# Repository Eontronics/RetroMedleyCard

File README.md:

# RetroMedleyCard
Repository containing the RetroMedleyCard hardware design files.

RetroMedleyCard is a buisiness card sized PCB created for the [Hackaday 2024 Business Card Contest](https://hackaday.io/contest/195949-2024-business-card-contest) that aims to run a range of emulators with support for USB controllers, and output to full sized monitors/TVs, while maintaining a thicnkess <=2.0mm.

The Hackaday.io project page for RetroMedleyCard may be found at https://hackaday.io/project/196328-retromedleycard, which includes images of the physical hardware and testing

# Limitations
The current (first) iteration of RetroMedleyCard is severely limited by the ~2MB of onboard RAM, and various other issues:
* It has been successfully tested running Gameboy emulation without audio output, however other emulators often cause the system to crash immediately.
* The connectors are all formed using specially shaped PCB structures in order to maintain a thin form-factor, however these often fail to make reliable contact for audio, USB-C and SD card connections.
* Display output is limited to ~52fps @320x240 in RGB565, due to difficulty moving pixel data from the RP2040 PIO into the frame-buffer while remaining syncronised with commands sent over the same interface

It is intended to run a modified version of [retro-go](https://github.com/ducalex/retro-go), however firmware is not yet provided as it is currently a mess of rushed tweaks in an attempt to get a functional device.

As a result of these limitations I do not see it being worthwhile to improve the firmware for this version of RetroMedleyCard, as future iterations should aim to adress the lack of available memory, for which a more complete firmware can be written.

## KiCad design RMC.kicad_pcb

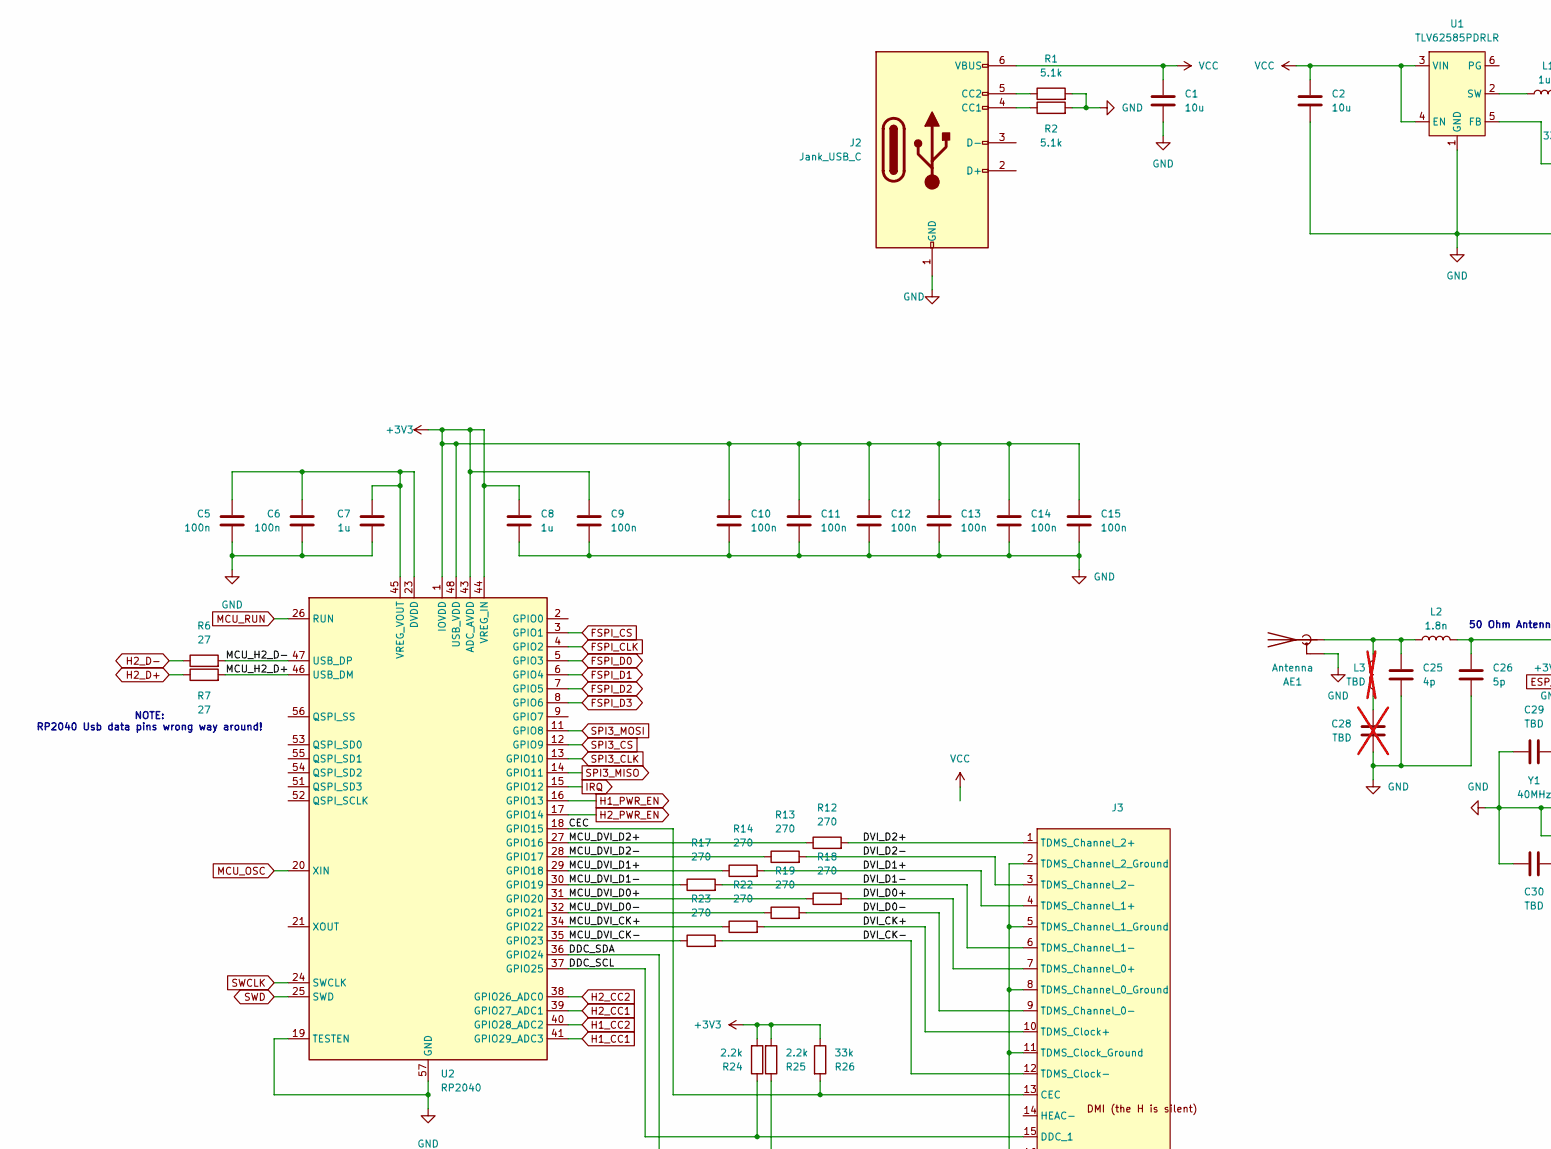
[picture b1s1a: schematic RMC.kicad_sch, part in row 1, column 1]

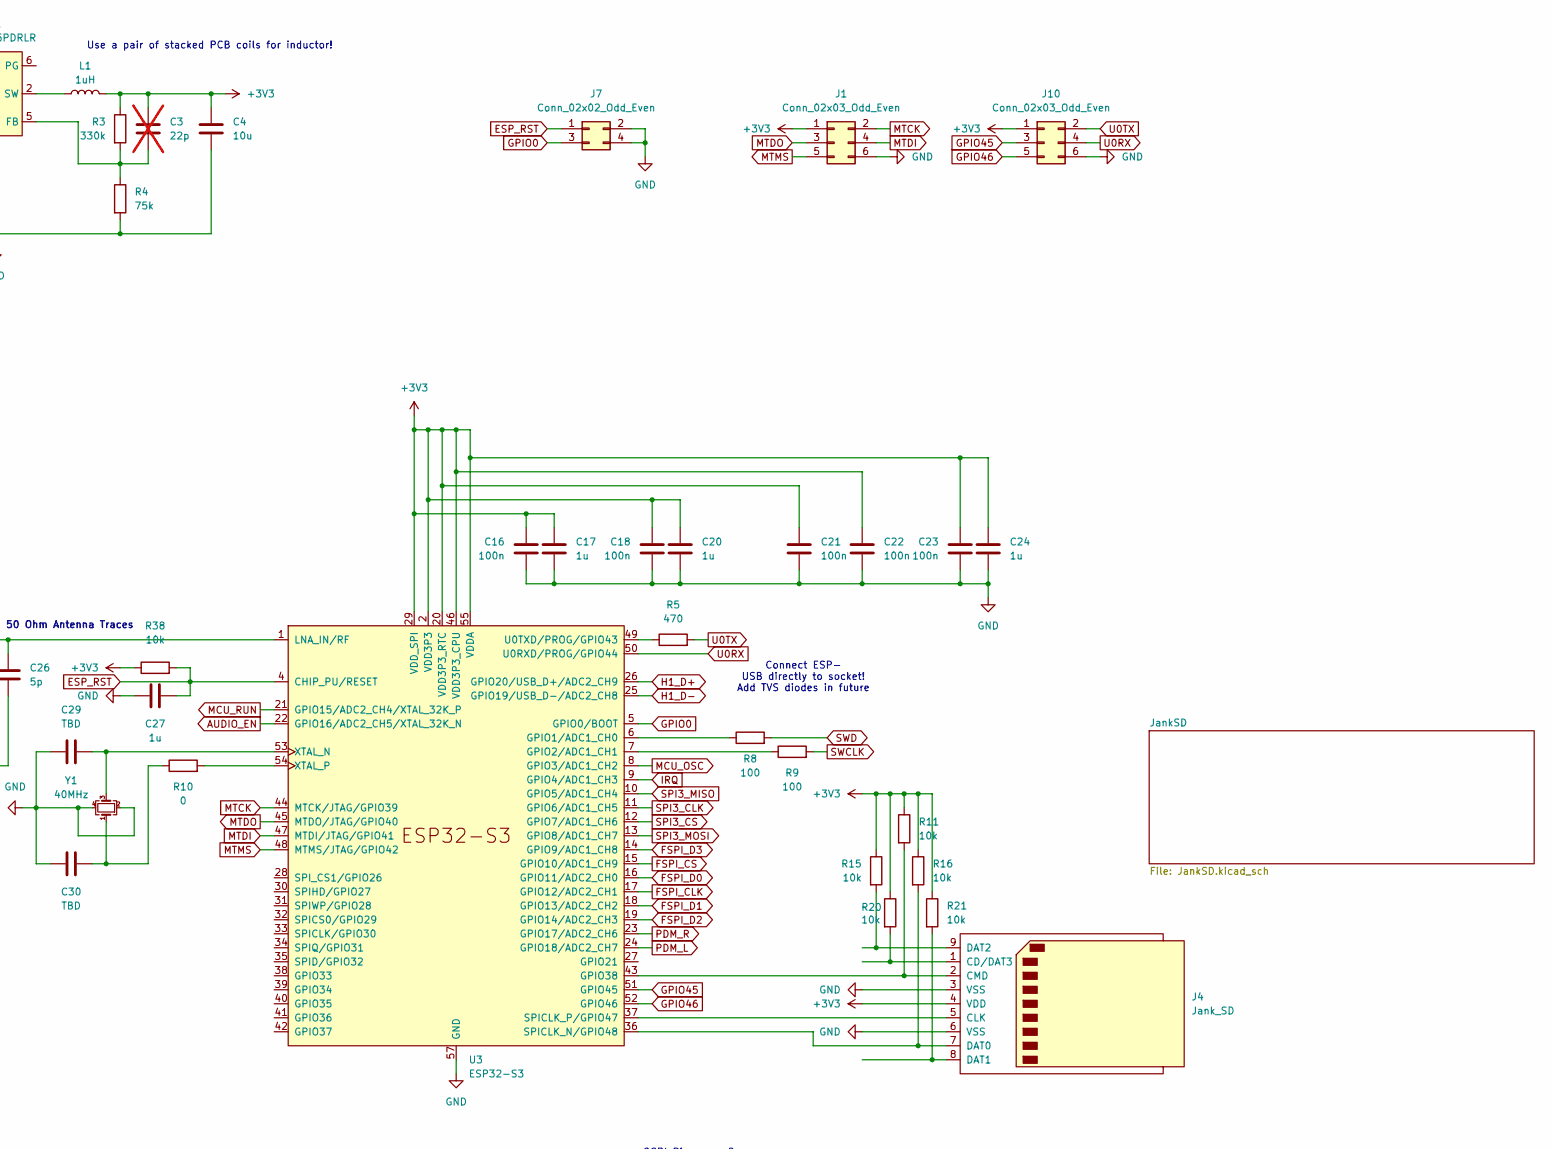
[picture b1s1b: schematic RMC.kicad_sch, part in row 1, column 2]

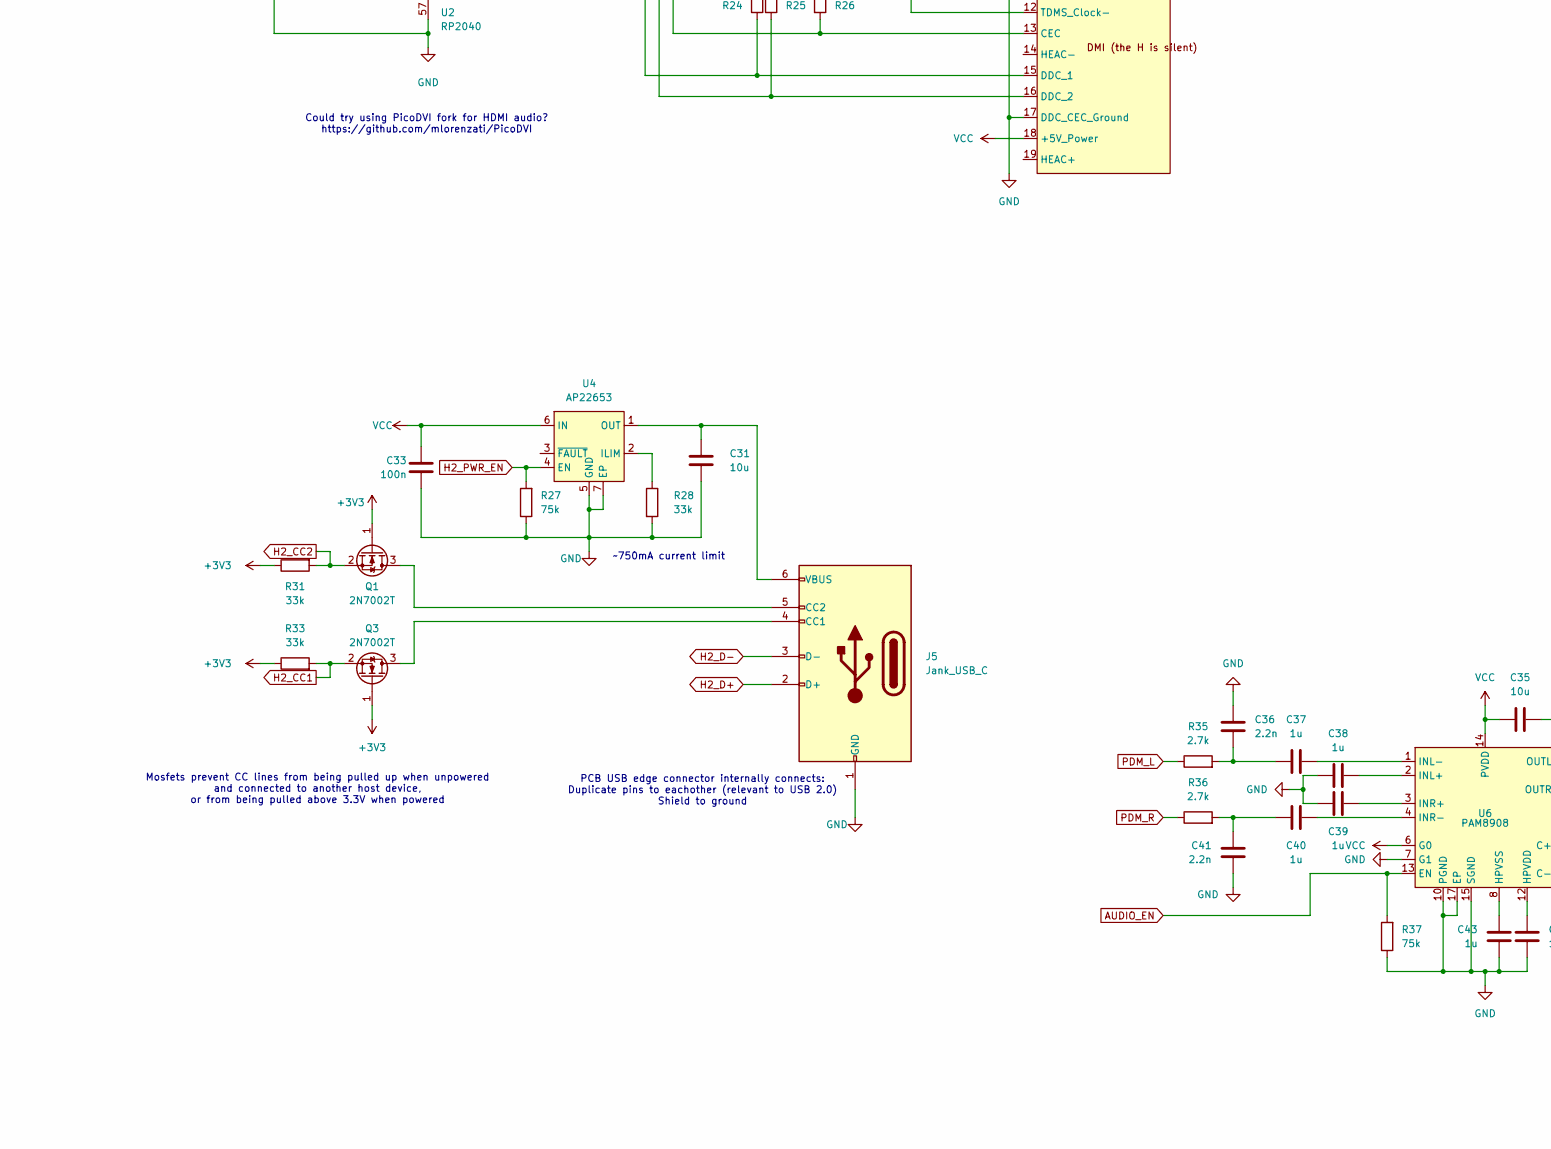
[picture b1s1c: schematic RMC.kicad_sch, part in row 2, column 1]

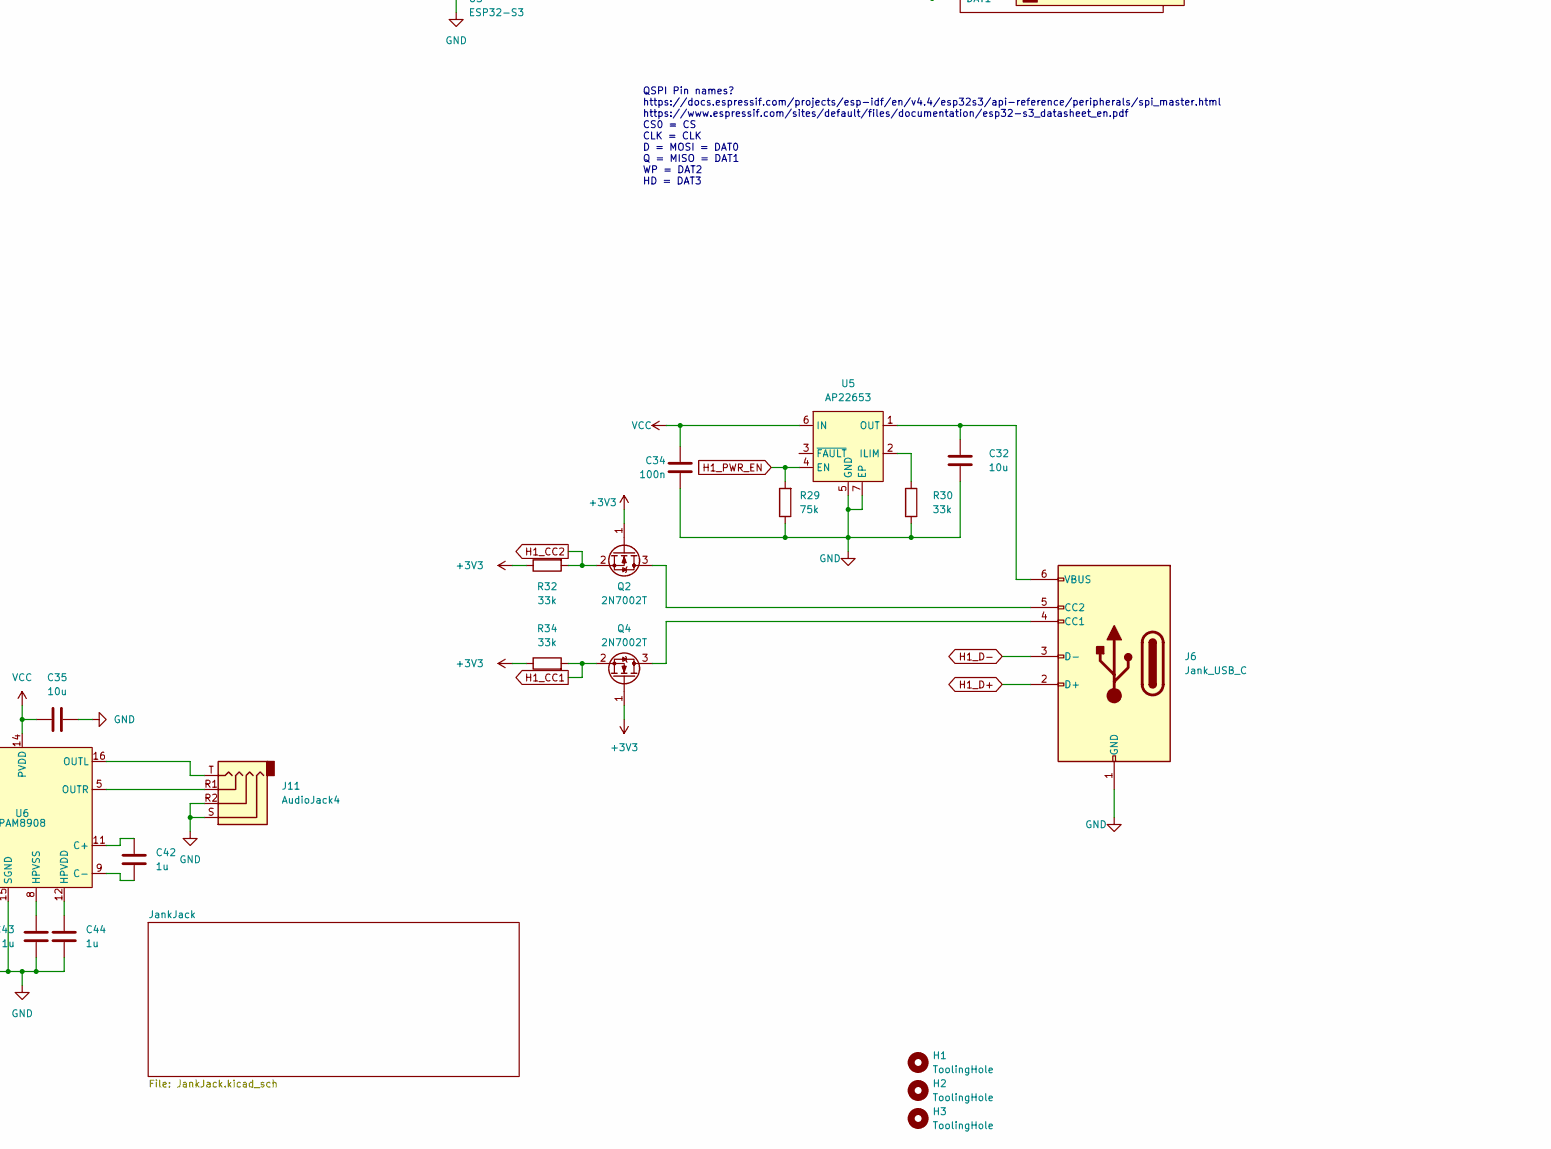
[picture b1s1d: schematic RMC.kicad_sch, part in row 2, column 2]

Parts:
AE1: Antenna; Texas_SWRA117D_2.4GHz_Right
C1, C2, C4, C31, C32, C35: 10u; C_0603_1608Metric
C3: 22p; C_0603_1608Metric; not fitted
C5, C6, C9, C10, C11, C12, C13, C14, C15, C16, C18, C21, C22, C23, C33, C34: 100n; C_0402_1005Metric
C7, C8, C17, C20, C24, C27, C37, C38, C39, C40, C42, C43, C44: 1u; C_0603_1608Metric
C25: 4p; C_0402_1005Metric
C26: 5p; C_0402_1005Metric
C28: TBD; C_0402_1005Metric; not fitted
C29, C30: TBD; C_0603_1608Metric
C36, C41: 2.2n; C_0603_1608Metric
H1, H2, H3: ToolingHole; JLC_Tooling_Hole
J1, J10: Conn_02x03_Odd_Even; PinHeader_2x03_P2.54mm_Vertical
J2, J5, J6: Jank_USB_C; JankUSBCB
J3: PBMI
J4: Jank_SD; JankSDB
J7: Conn_02x02_Odd_Even; PinHeader_2x02_P2.54mm_Vertical
J11: AudioJack4; JankJackB
L1: 1uH; 1uH_12.8mm_PCB_Coil
L2: 1.8n; L_0402_1005Metric
L3: TBD; L_0402_1005Metric; not fitted
Q1, Q2, Q3, Q4: 2N7002T; SOT-523
R1, R2: 5.1k; R_0603_1608Metric
R3: 330k; R_0603_1608Metric
R4, R27, R29, R37: 75k; R_0603_1608Metric
R5: 470; R_0603_1608Metric
R6, R7: 27; R_0603_1608Metric
R8, R9: 100; R_0603_1608Metric
R10: 0; R_0603_1608Metric
R11, R15, R16, R20, R21, R38: 10k; R_0603_1608Metric
R12, R13, R14, R17, R18, R19, R22, R23: 270; R_0603_1608Metric
R24, R25: 2.2k; R_0603_1608Metric
R26, R28, R30, R31, R32, R33, R34: 33k; R_0603_1608Metric
R35, R36: 2.7k; R_0603_1608Metric
U1: TLV62585PDRLR; SOT-563
U2: RP2040; QFN-56-1EP_7x7mm_P0.4mm_EP3.2x3.2mm
U3: ESP32-S3; QFN-56-1EP_7x7mm_P0.4mm_EP5.6x5.6mm
U4, U5: AP22653; DFN-6-1EP_2x2mm_P0.65mm_EP1x1.6mm
U6: PAM8908; QFN-16-1EP_3x3mm_P0.5mm_EP1.7x1.7mm
Y1: 40MHz; Crystal_SMD_3225-4Pin_3.2x2.5mm

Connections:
+3V3: C3.1, C4.1, C8.2, C9.1, C10.1, C11.1, C12.1, C13.1, C14.1, C15.1, C16.2, C17.2, C18.2, C20.2, C21.2, C22.2, C23.2, C24.2, J1.1, J4.4 (VDD), J10.1, L1.1, Q1.1 (G), Q2.1 (G), Q3.1 (G), Q4.1 (G), R3.1, R11.1, R15.1, R16.1, R20.1, R21.1, R24.2, R25.2, R26.1, R31.1, R32.1, R33.1, R34.1, R38.1, U2.1 (IOVDD), U2.10 (IOVDD), U2.22 (IOVDD), U2.33 (IOVDD), U2.42 (IOVDD), U2.43 (ADC_AVDD), U2.44 (VREG_IN), U2.48 (USB_VDD), U2.49 (IOVDD), U3.2 (VDD3P3), U3.3 (VDD3P3), U3.20 (VDD3P3_RTC), U3.29 (VDD_SPI), U3.46 (VDD3P3_CPU), U3.55 (VDDA), U3.56 (VDDA)
/CEC: J3.13 (CEC), R26.2, U2.18 (GPIO15)
/DDC_SCL: J3.15 (DDC_1), R24.1, U2.37 (GPIO25)
/DDC_SDA: J3.16 (DDC_2), R25.1, U2.36 (GPIO24)
/DVI_CK+: J3.10 (TDMS_Clock+), R22.2
/DVI_CK-: J3.12 (TDMS_Clock-), R23.2
/DVI_D0+: J3.7 (TDMS_Channel_0+), R18.2
/DVI_D0-: J3.9 (TDMS_Channel_0-), R19.2
/DVI_D1+: J3.4 (TDMS_Channel_1+), R14.2
/DVI_D1-: J3.6 (TDMS_Channel_1-), R17.2
/DVI_D2+: J3.1 (TDMS_Channel_2+), R12.2
/DVI_D2-: J3.3 (TDMS_Channel_2-), R13.2
/MCU_DVI_CK+: R22.1, U2.34 (GPIO22)
/MCU_DVI_CK-: R23.1, U2.35 (GPIO23)
/MCU_DVI_D0+: R18.1, U2.31 (GPIO20)
/MCU_DVI_D0-: R19.1, U2.32 (GPIO21)
/MCU_DVI_D1+: R14.1, U2.29 (GPIO18)
/MCU_DVI_D1-: R17.1, U2.30 (GPIO19)
/MCU_DVI_D2+: R12.1, U2.27 (GPIO16)
/MCU_DVI_D2-: R13.1, U2.28 (GPIO17)
/MCU_H2_D+: R7.2, U2.46 (USB_DM)
/MCU_H2_D-: R6.2, U2.47 (USB_DP)
AUDIO_EN: R37.2, U3.22 (GPIO16/ADC2_CH5/XTAL_32K_N), U6.13 (EN)
ESP_RST: C27.1, J7.1, R38.2, U3.4 (CHIP_PU/RESET)
FSPI_CLK: U2.4 (GPIO2), U3.17 (GPIO12/ADC2_CH1)
FSPI_CS: U2.3 (GPIO1), U3.15 (GPIO10/ADC1_CH9)
FSPI_D0: U2.5 (GPIO3), U3.16 (GPIO11/ADC2_CH0)
FSPI_D1: U2.6 (GPIO4), U3.18 (GPIO13/ADC2_CH2)
FSPI_D2: U2.7 (GPIO5), U3.19 (GPIO14/ADC2_CH3)
FSPI_D3: U2.8 (GPIO6), U3.14 (GPIO9/ADC1_CH8)
GND: AE1.2 (Shield), C1.1, C2.2, C4.2, C5.2, C6.2, C7.2, C8.1, C9.2, C10.2, C11.2, C12.2, C13.2, C14.2, C15.2, C16.1, C17.1, C18.1, C20.1, C21.1, C22.1, C23.1, C24.1, C25.2, C26.2, C27.2, C28.2, C29.1, C30.1, C31.2, C32.2, C33.2, C34.2, C35.1, C36.1, C38.1, C39.1, C41.2, C43.1, C44.1, J1.6, J2.1 (GND), J3.2 (TDMS_Channel_2_Ground), J3.5 (TDMS_Channel_1_Ground), J3.8 (TDMS_Channel_0_Ground), J3.11 (TDMS_Clock_Ground), J3.17 (DDC_CEC_Ground), J4.3 (VSS), J4.6 (VSS), J5.1 (GND), J6.1 (GND), J7.2, J7.4, J10.6, J11.R2, J11.S, R1.2, R2.2, R4.2, R27.1, R28.2, R29.1, R30.2, R37.1, U1.1 (GND), U2.19 (TESTEN), U2.57 (GND), U3.57 (GND), U4.5 (GND), U4.7 (EP), U5.5 (GND), U5.7 (EP), U6.7 (G1), U6.10 (PGND), U6.15 (SGND), U6.17 (EP), Y1.2, Y1.4
GPIO0: J7.3, U3.5 (GPIO0/BOOT)
GPIO45: J10.3, U3.51 (GPIO45)
GPIO46: J10.5, U3.52 (GPIO46)
H1_CC1: Q4.2 (S), R34.2, U2.41 (GPIO29_ADC3)
H1_CC2: Q2.2 (S), R32.2, U2.40 (GPIO28_ADC2)
H1_D+: J6.2 (D+), U3.26 (GPIO20/USB_D+/ADC2_CH9)
H1_D-: J6.3 (D-), U3.25 (GPIO19/USB_D-/ADC2_CH8)
H1_PWR_EN: R29.2, U2.16 (GPIO13), U5.4 (EN)
H2_CC1: Q3.2 (S), R33.2, U2.39 (GPIO27_ADC1)
H2_CC2: Q1.2 (S), R31.2, U2.38 (GPIO26_ADC0)
H2_D+: J5.2 (D+), R7.1
H2_D-: J5.3 (D-), R6.1
H2_PWR_EN: R27.2, U2.17 (GPIO14), U4.4 (EN)
IRQ: U2.15 (GPIO12), U3.9 (GPIO4/ADC1_CH3)
MCU_OSC: U2.20 (XIN), U3.8 (GPIO3/ADC1_CH2)
MCU_RUN: U2.26 (RUN), U3.21 (GPIO15/ADC2_CH4/XTAL_32K_P)
MTCK: J1.2, U3.44 (MTCK/JTAG/GPIO39)
MTDI: J1.4, U3.47 (MTDI/JTAG/GPIO41)
MTDO: J1.3, U3.45 (MTDO/JTAG/GPIO40)
MTMS: J1.5, U3.48 (MTMS/JTAG/GPIO42)
unnamed: AE1.1 (A), C25.1, L2.1, L3.2
unnamed: C28.1, L3.1
unnamed: C30.2, R10.1, Y1.1
unnamed: C36.2, C37.1, R35.2
unnamed: C40.1, C41.1, R36.2
unnamed: J2.4 (CC1), R2.1
unnamed: J2.5 (CC2), R1.1
unnamed: J4.1 (CD/DAT3), R20.2
unnamed: J4.5 (CLK), U3.37 (SPICLK_P/GPIO47)
unnamed: J4.2 (CMD), R11.2, U3.43 (GPIO38)
unnamed: J4.7 (DAT0), R16.2, U3.36 (SPICLK_N/GPIO48)
unnamed: J4.8 (DAT1), R21.2
unnamed: J4.9 (DAT2), R15.2
unnamed: J5.4 (CC1), Q3.3 (D)
unnamed: J5.5 (CC2), Q1.3 (D)
unnamed: C31.1, J5.6 (VBUS), U4.1 (OUT)
unnamed: J6.4 (CC1), Q4.3 (D)
unnamed: J6.5 (CC2), Q2.3 (D)
unnamed: C32.1, J6.6 (VBUS), U5.1 (OUT)
unnamed: C3.2, R3.2, R4.1, U1.5 (FB)
unnamed: L1.2, U1.2 (SW)
unnamed: C5.1, C6.1, C7.1, U2.23 (DVDD), U2.45 (VREG_VOUT), U2.50 (DVDD)
unnamed: R8.1, U3.6 (GPIO1/ADC1_CH0)
unnamed: R9.1, U3.7 (GPIO2/ADC1_CH1)
unnamed: C26.1, L2.2, U3.1 (LNA_IN/RF)
unnamed: R5.1, U3.49 (U0TXD/PROG/GPIO43)
unnamed: C29.2, U3.53 (XTAL_N), Y1.3
unnamed: R10.2, U3.54 (XTAL_P)
unnamed: R28.1, U4.2 (ILIM)
unnamed: R30.1, U5.2 (ILIM)
unnamed: C42.2, U6.11 (C+)
unnamed: C42.1, U6.9 (C-)
unnamed: C44.2, U6.12 (HPVDD)
unnamed: C43.2, U6.8 (HPVSS)
unnamed: C38.2, U6.2 (INL+)
unnamed: C37.2, U6.1 (INL-)
unnamed: C39.2, U6.3 (INR+)
unnamed: C40.2, U6.4 (INR-)
unnamed: J11.T, U6.16 (OUTL)
unnamed: J11.R1, U6.5 (OUTR)
PDM_L: R35.1, U3.24 (GPIO18/ADC2_CH7)
PDM_R: R36.1, U3.23 (GPIO17/ADC2_CH6)
SPI3_CLK: U2.13 (GPIO10), U3.11 (GPIO6/ADC1_CH5)
SPI3_CS: U2.12 (GPIO9), U3.12 (GPIO7/ADC1_CH6)
SPI3_MISO: U2.14 (GPIO11), U3.10 (GPIO5/ADC1_CH4)
SPI3_MOSI: U2.11 (GPIO8), U3.13 (GPIO8/ADC1_CH7)
SWCLK: R9.2, U2.24 (SWCLK)
SWD: R8.2, U2.25 (SWD)
U0RX: J10.4, U3.50 (U0RXD/PROG/GPIO44)
U0TX: J10.2, R5.2
VCC: C1.2, C2.1, C33.1, C34.1, C35.2, J2.6 (VBUS), J3.18 (+5V_Power), U1.3 (VIN), U1.4 (EN), U4.6 (IN), U5.6 (IN), U6.6 (G0), U6.14 (PVDD)

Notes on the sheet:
QSPI Pin names? https://docs.espressif.com/projects/esp-idf/en/v4.4/esp32s3/api-reference/peripherals/spi_master.html https://www.espressif.com/sites/default/files/documentation/esp32-s3_datasheet_en.pdf CS0 = CS CLK = CLK D = MOSI = DAT0 Q = MISO = DAT1 WP = DAT2 HD = DAT3
Use a pair of stacked PCB coils for inductor!
~750mA current limit
Connect ESP- USB directly to socket! Add TVS diodes in future
Could try using PicoDVI fork for HDMI audio? https://github.com/mlorenzati/PicoDVI
50 Ohm Antenna Traces
Mosfets prevent CC lines from being pulled up when unpowered and connected to another host device, or from being pulled above 3.3V when powered
NOTE: RP2040 Usb data pins wrong way around!
PCB USB edge connector internally connects: Duplicate pins to eachother (relevant to USB 2.0) Shield to ground

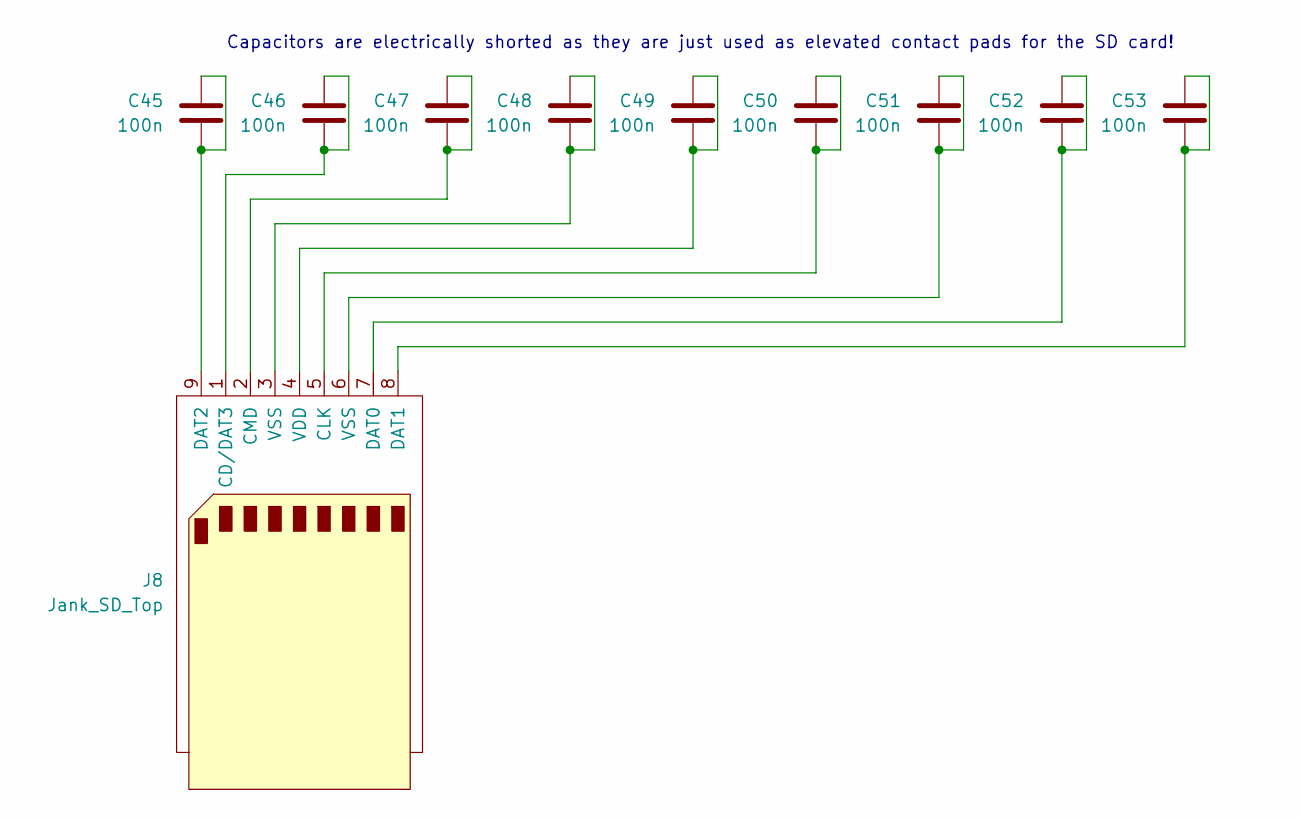
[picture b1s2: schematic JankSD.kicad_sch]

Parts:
C45, C46, C47, C48, C49, C50, C51, C52, C53: 100n; C_0603_1608Metric
J8: Jank_SD_Top; JankSDT

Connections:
unnamed: C48.1, C48.2, J8.3 (VSS)
unnamed: C51.1, C51.2, J8.6 (VSS)
unnamed: C46.1, C46.2, J8.1 (CD/DAT3)
unnamed: C50.1, C50.2, J8.5 (CLK)
unnamed: C47.1, C47.2, J8.2 (CMD)
unnamed: C52.1, C52.2, J8.7 (DAT0)
unnamed: C53.1, C53.2, J8.8 (DAT1)
unnamed: C45.1, C45.2, J8.9 (DAT2)
unnamed: C49.1, C49.2, J8.4 (VDD)

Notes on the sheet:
Capacitors are electrically shorted as they are just used as elevated contact pads for the SD card!

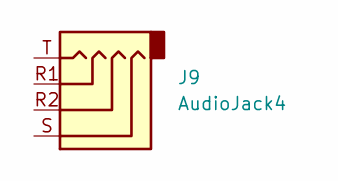
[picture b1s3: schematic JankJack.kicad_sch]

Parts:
J9: AudioJack4; JankJackT

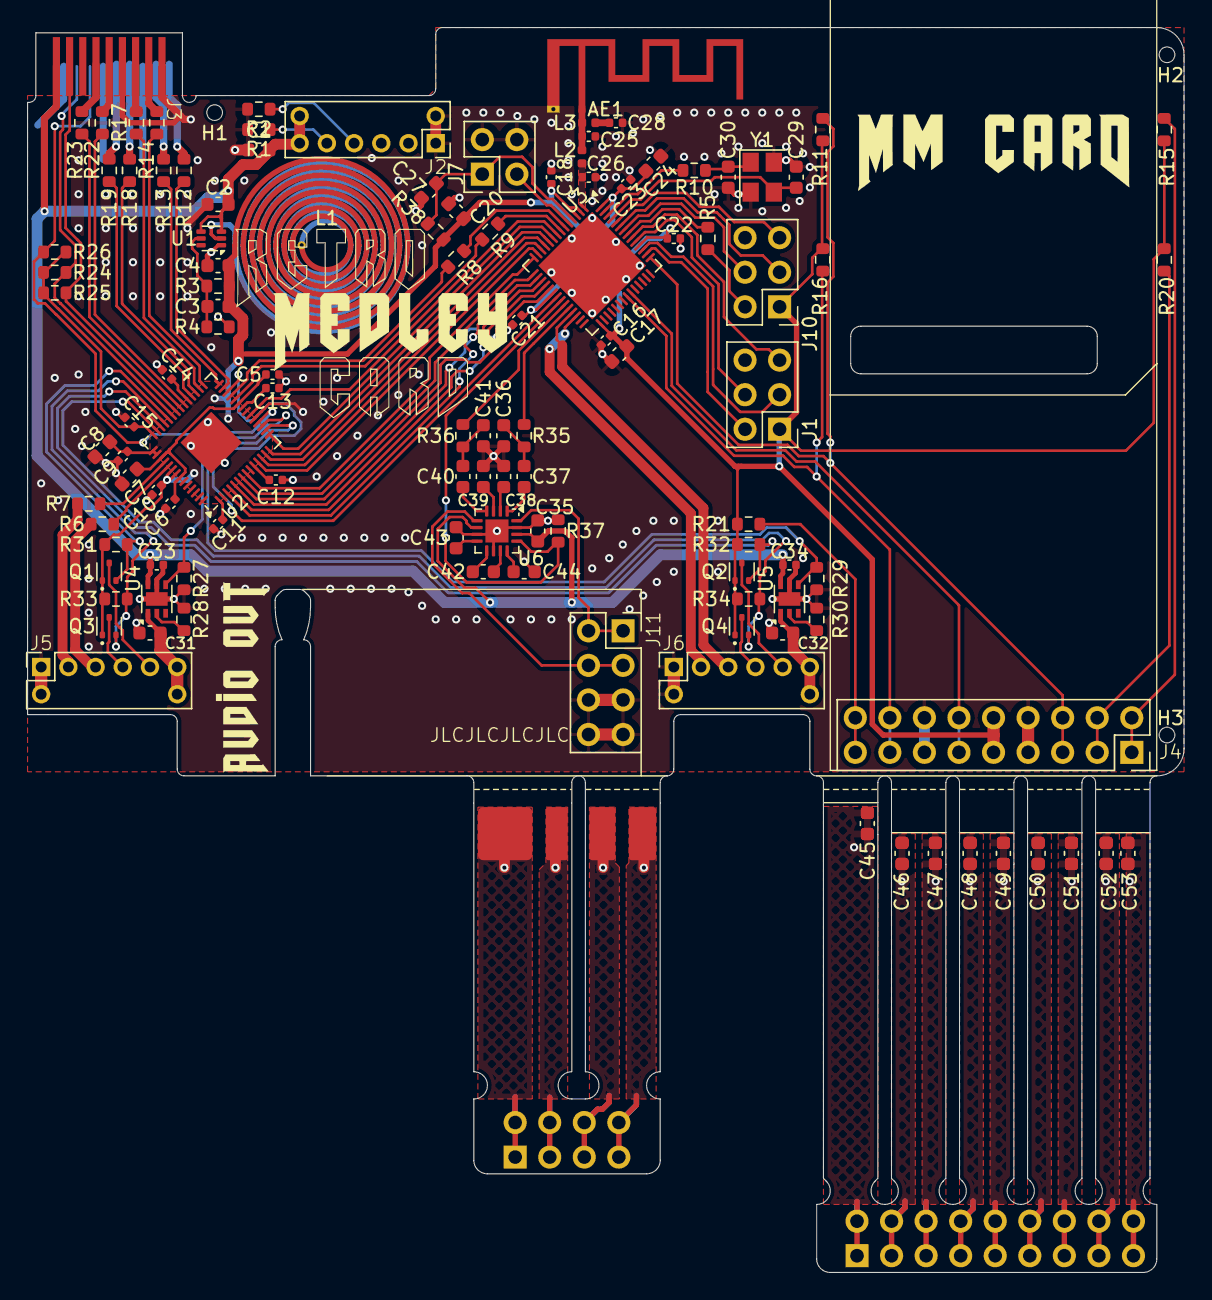
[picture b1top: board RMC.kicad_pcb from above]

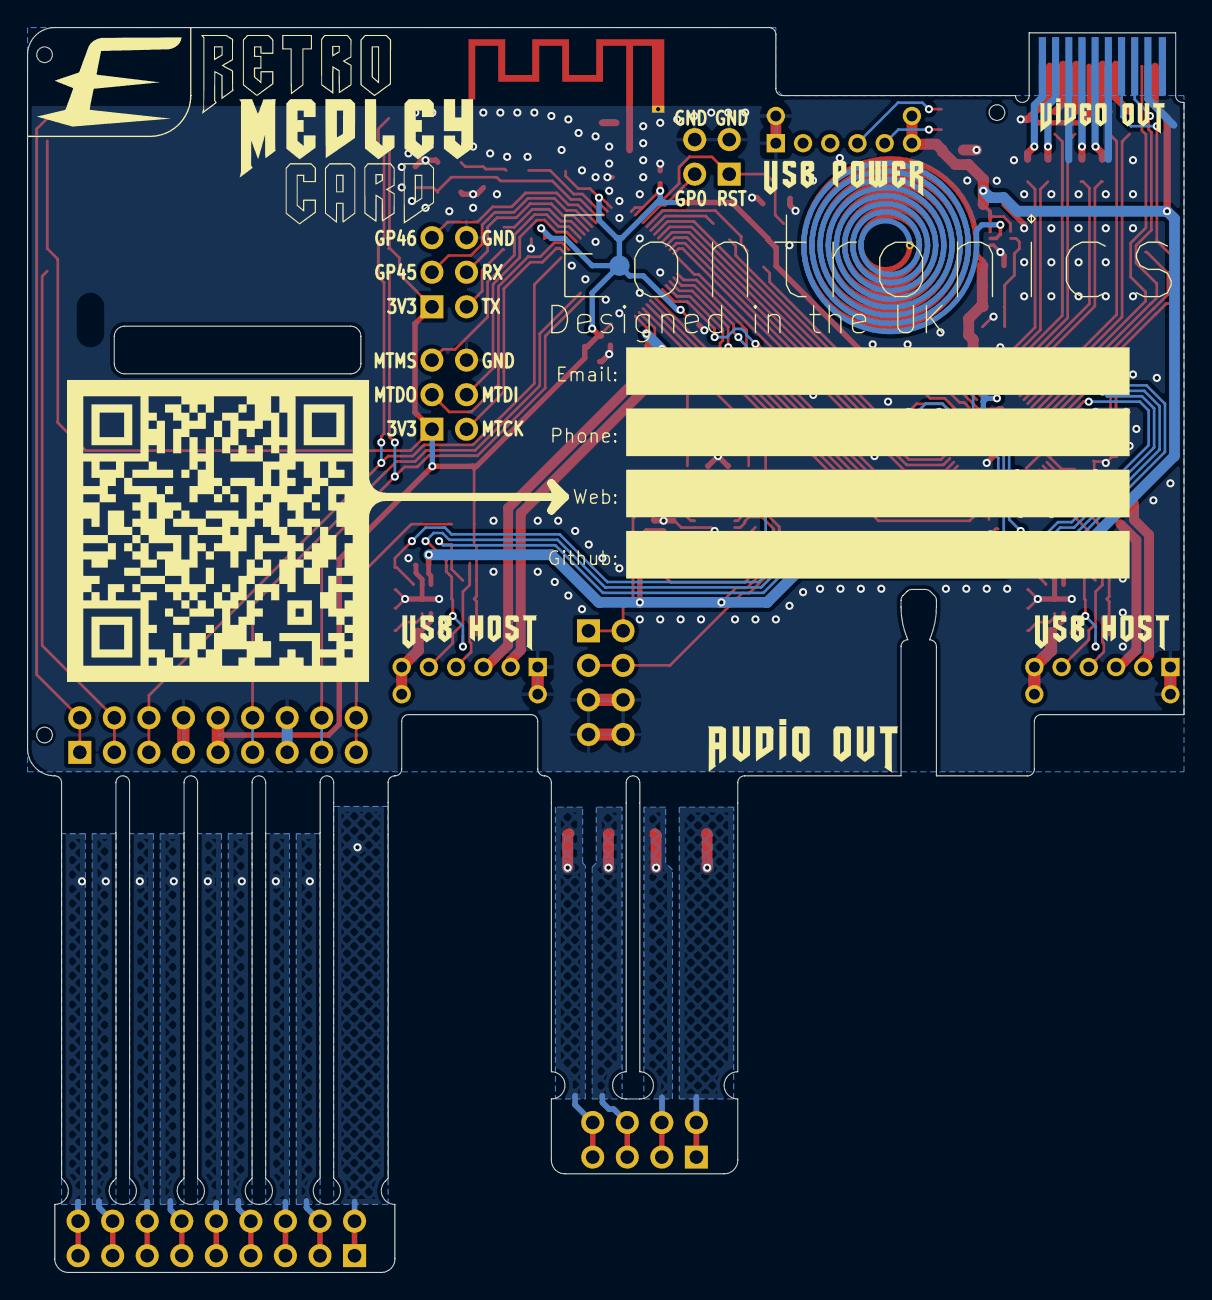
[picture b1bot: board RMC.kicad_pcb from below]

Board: 2 copper layers, 85.0 x 91.5 mm, 120 parts (3 on the bottom side), 111 nets.

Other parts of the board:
QR*****: Example_QR_Code_22mm

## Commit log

2024-06-30 [main] initial commit
